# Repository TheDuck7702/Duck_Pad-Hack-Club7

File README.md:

# Duck_Pad-Hack-Club
The hackpad i made for Highway for Hackclub. 
Slack info:
username: Shais5738
Email: shais5738@gmail.com

Overview
A compact 6-key and knob keyboard designed for quick access to common functions like volume control, open calculator or other apps, and other shortcuts.

Features
- 6 customizable keys for various shortcuts.
- Rotary knob for volume adjustment.
- Compact and ergonomic design for easy use.

BOM

- 2x	SK6812				LED_SMD:LED_SK6812MINI_PLCC4_3.5x3.5mm_P1.75mm
- 1x	SW7_RotaryEncoder    Rotary_Encoder:RotaryEncoder_Alps_EC11E_Vertical_H20mm
- 6x	SW_Push				Button_Switch_Keyboard:SW_Cherry_MX_1.00u_PCB	~
- 1x	XIAO-RP2040-DIP				opl:XIAO-RP2040-DIP

Notes:
Hey, this is my first formal sudmition of an acc project for a hackathon, so i been told to rly take time in the readme. I got recomeded to go w/ a freind to curcit island. There i joined slack and found out about many programs liek solder and highway. I finished Solder and it was rly fun. I learn alot abotu how to build and set up the structure of the Pcb, which aslo helped me here, and understood how much work goes into these. I started the hack-pad project on Monday so 2 June, but didn't start to do anything until June 4 or 5. I wanted it wo be simple, js following the toutorial while adding my own little things. I have added 6 switches, and a knob. The 6 switches you can set to be differnt keys like prtsc (screenshot) or open calc or just like some numbers so u can enter ur password quicker. The knob will be for like vol control. Doing the scematics and pcb was easy but i have no idea what im doing for the codeing. Like i know python and c++ but i just dont know where to start. I looked at the slack #hackpad and i got a basic idea for it. I think theres 2 ways u can code ts, one way is a type of python called MicroPython(KMK) and another way called(QMK), which is run on C++. I think ill code it in the KMK first, as the slack people said its easier. I might code it in QMK for the experance for my next project.w

Photos:

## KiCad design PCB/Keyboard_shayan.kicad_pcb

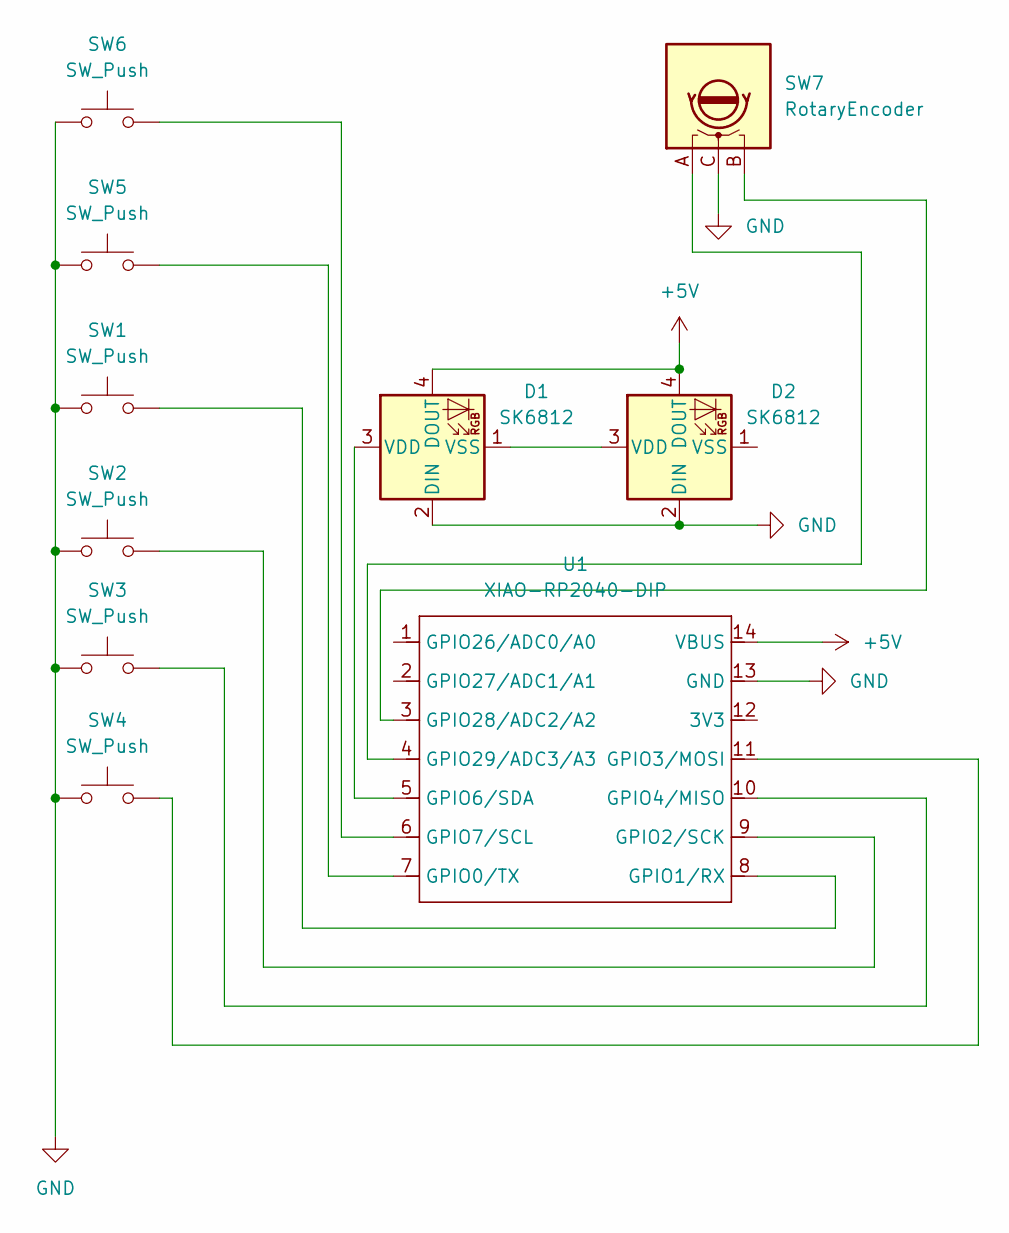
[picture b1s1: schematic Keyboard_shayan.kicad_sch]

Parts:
D1, D2: SK6812; LED_SK6812MINI_PLCC4_3.5x3.5mm_P1.75mm
SW1, SW2, SW3, SW4, SW5, SW6: SW_Push; SW_Cherry_MX_1.00u_PCB
SW7: RotaryEncoder; RotaryEncoder_Alps_EC11E_Vertical_H20mm
U1: XIAO-RP2040-DIP

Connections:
+5V: D1.4 (DOUT), D2.4 (DOUT), U1.14 (VBUS)
GND: D1.2 (DIN), D2.2 (DIN), SW1.1, SW2.1, SW3.1, SW4.1, SW5.1, SW6.1, SW7.C, U1.13 (GND)
unnamed: D1.3 (VDD), U1.5 (GPIO6/SDA)
unnamed: D1.1 (VSS), D2.3 (VDD)
unnamed: SW5.2, U1.7 (GPIO0/TX)
unnamed: SW1.2, U1.8 (GPIO1/RX)
unnamed: SW2.2, U1.9 (GPIO2/SCK)
unnamed: SW4.2, U1.11 (GPIO3/MOSI)
unnamed: SW3.2, U1.10 (GPIO4/MISO)
unnamed: SW6.2, U1.6 (GPIO7/SCL)
unnamed: SW7.B, U1.3 (GPIO28/ADC2/A2)
unnamed: SW7.A, U1.4 (GPIO29/ADC3/A3)

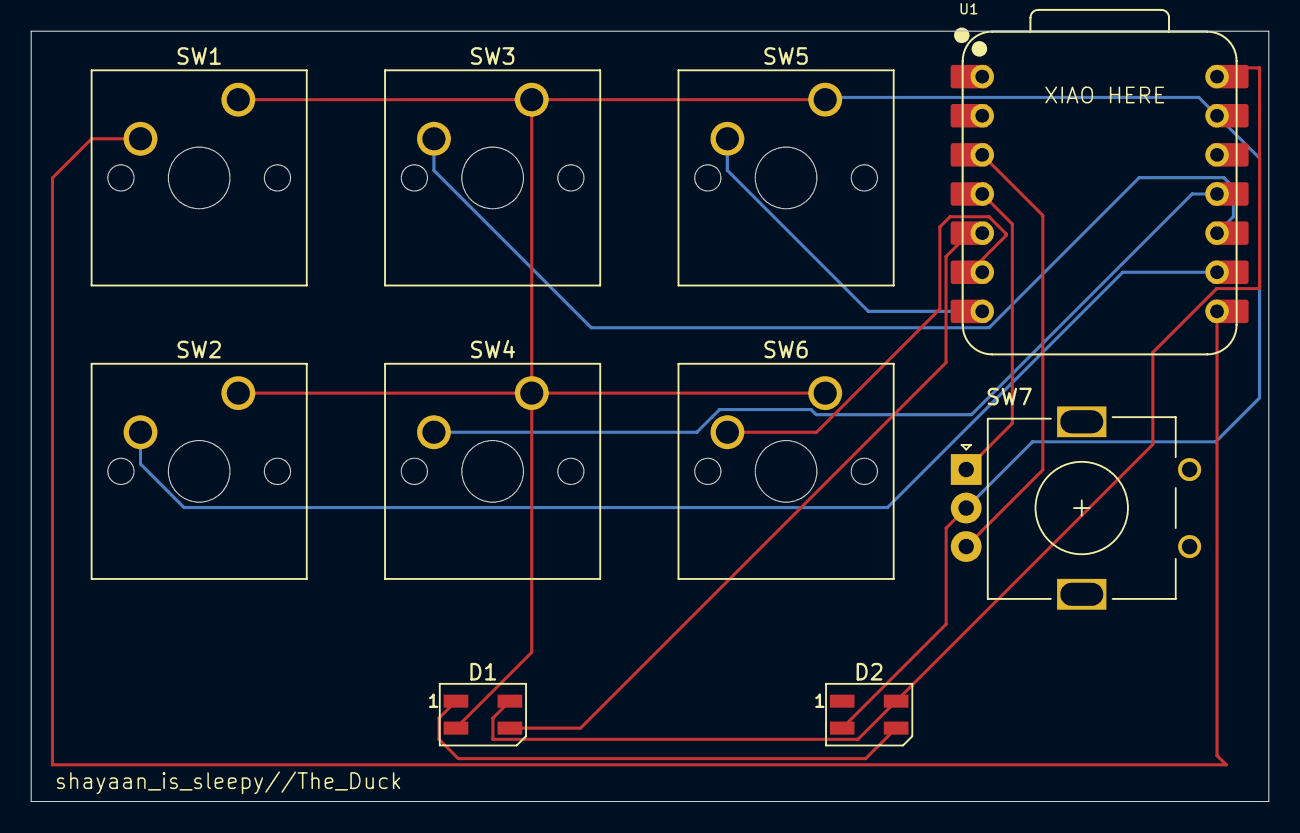
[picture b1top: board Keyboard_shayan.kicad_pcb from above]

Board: 2 copper layers, 80.3 x 50.0 mm, 10 parts (0 on the bottom side), 12 nets.

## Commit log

2025-06-11 mango mango mango mango phonk (those who know)
